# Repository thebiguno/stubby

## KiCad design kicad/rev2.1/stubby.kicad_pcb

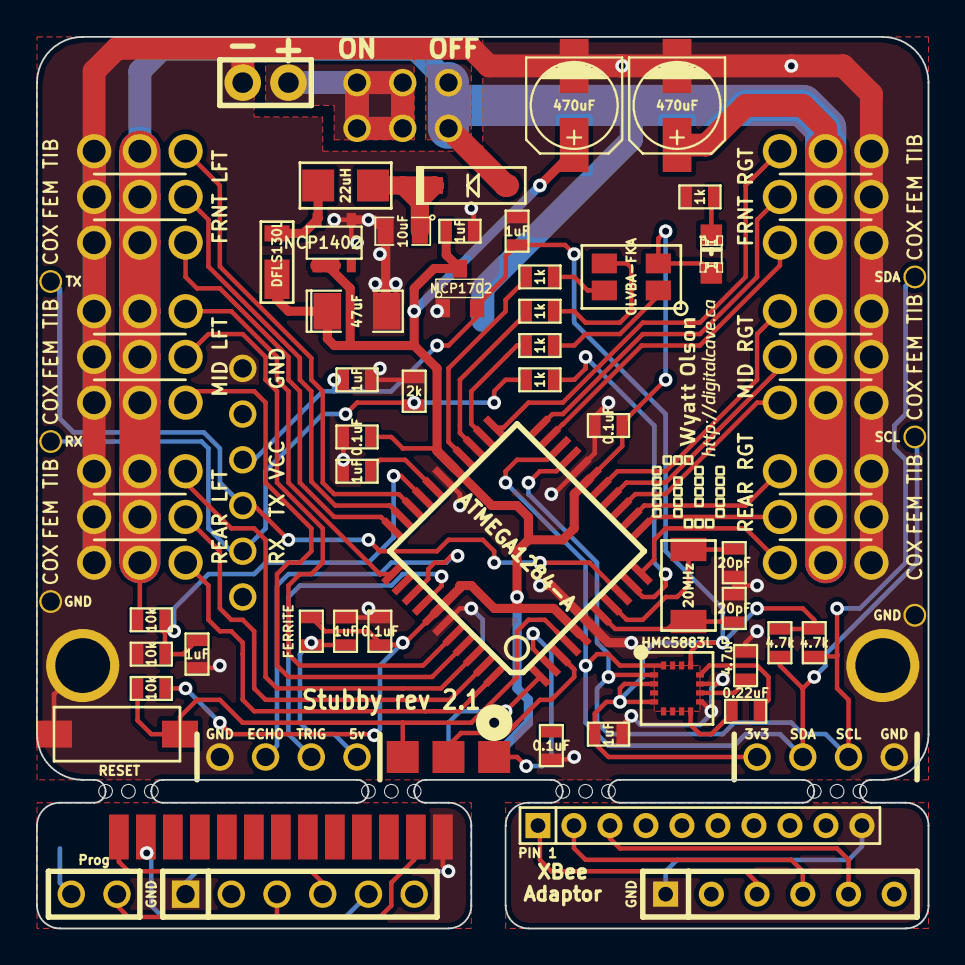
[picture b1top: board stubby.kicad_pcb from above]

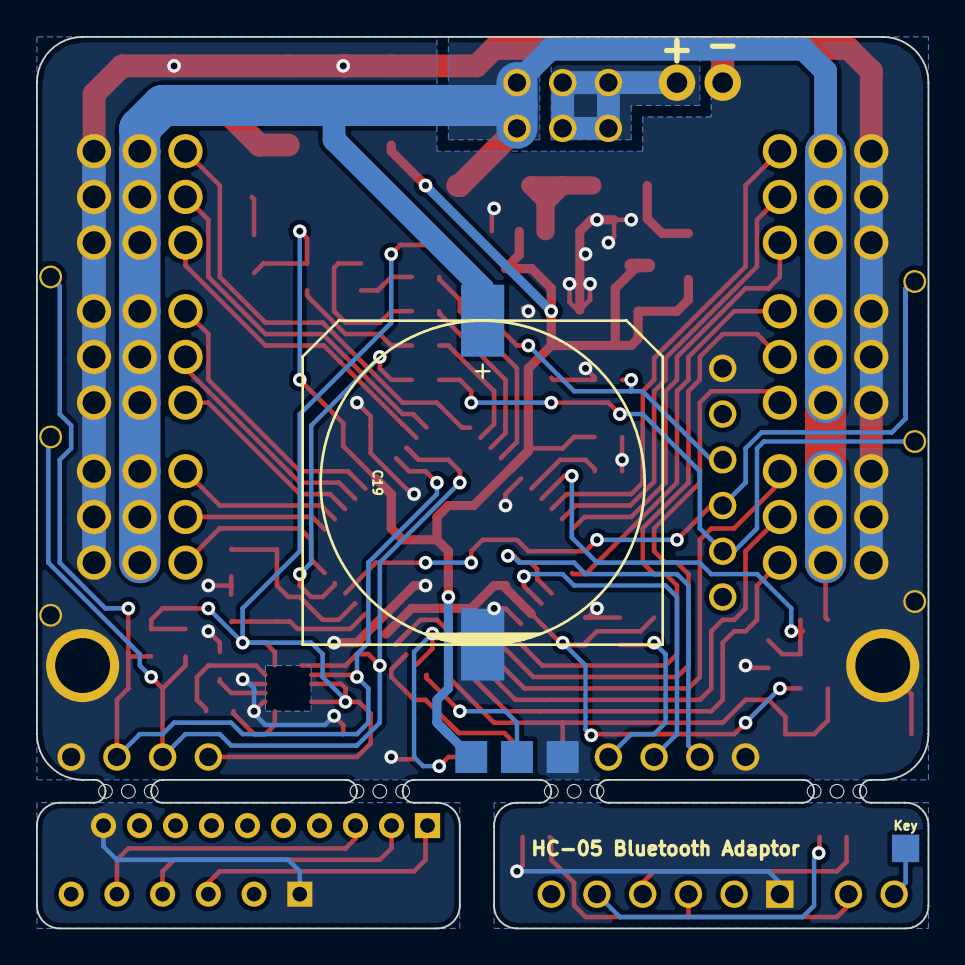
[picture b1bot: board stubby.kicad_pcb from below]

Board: 2 copper layers, 49.5 x 49.5 mm, 74 parts (2 on the bottom side), 60 nets.

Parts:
1PIN, 1PIN#2, 1PIN#3, 1PIN#4, 1PIN#5, 1PIN#6, 1PIN#7, 1PIN#8: P***; 1pin
C1: 10uF; SM0805
C2, C3, C6, C15, C16, C17, C18: 1uF; SM0603_VALUE
C4: 47uF; SM1206POL
C5, C20: 470uF; c_elec_5x5.3
C7: 4.7uF; SM0603_VALUE
C8, C9: 20pF; SM0603_VALUE
C10: 0.22uF; SM0603_VALUE
C11, C12, C13, C14: 0.1uF; SM0603_VALUE
C19: 6800µF; c_elec_18x18
D1: 1N4148W; SOD-123_DIODE
D2: DFLS130L; POWERDI_123
D3: LED; LED-0805-MARKED_ANODE
D4: CLVBA-FKA; 4-PLCC
IC1: ATMEGA1284-A; TQFP44
L1: 22uH; SM1007
L2: FERRITE; SM0603_VALUE
P1, P6, P11: CONN_6; SIL-6
P2, P10: CONN_4; SIL-4
P3: CONN_13; HC05_Edge
P4: CONN_2; SIL-2
P5: CONN_1; SIL-1
P7: CONN_10; SIL-10
P8: BATT (4.8V-6V); SIL-2
P9: PROG; ISP_EDGE
R1, R2: 4.7k; SM0603_VALUE
R3, R5, R6: 10k; SM0603_VALUE
R4, R7, R9, R10, R11: 1k; SM0603_VALUE
R8: 2k; SM0603_VALUE
S1: FRNT LFT; HEX_LEG
S2: FRNT RGT; HEX_LEG_REVERSE
S3: MID LFT; HEX_LEG
S4: MID RGT; HEX_LEG_REVERSE
S5: REAR LFT; HEX_LEG
S6: REAR RGT; HEX_LEG_REVERSE
SW1: SW_PUSH; SW_6x3
SW2: DPDT
U1: HMC5883L; LPCC-16
VAL: DIGITALCAVE_LOGO_WIDE_SMALL
VR1: MCP1702; SOT23
VR2: NCP1402; SOT23-5
X1: 20MHz; CRYSTAL_SMD_5x3.2
mouse_bites: VAL**; mouse_bites
mouse_bites#2, mouse_bites#3, mouse_bites#4: VAL**; mouse_bites

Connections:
+3.3V: C2.1, C15.1, C18.2, P2.1, P11.3, R1.2, R2.2, U1.2, U1.4, U1.13, VR1.3
+5V: C3.1, C4.1, C5.1, C11.1, C12.1, C13.1, D2.2, D3.1, D4.2, IC1.5, IC1.17, IC1.27, IC1.38, L2.2, P9.2, R3.1, VR1.2, VR2.1, VR2.2
+BATT: C19.1, C20.1, D1.1, R5.1, S1.4, S1.5, S1.6, S2.4, S2.5, S2.6, S3.4, S3.5, S3.6, S4.4, S4.5, S4.6, S5.4, S5.5, S5.6, S6.4, S6.5, S6.6, SW2.3, SW2.6
/ADC_BATTERY_METER: C16.2, IC1.30, R5.2, R6.2
/AREF: C6.2, IC1.29
/AVR_RX: 1PIN#6.1, IC1.9, P11.4
/AVR_TX: IC1.10, R7.1
/BATTERY: P8.1, SW2.1, SW2.2, SW2.4, SW2.5
/BLUETOOTH_GND: P1.1, P3.13
/DIST_ECHO: IC1.36, P10.3
/DIST_TRIG: IC1.37, P10.2
/I2C_SCL: 1PIN#3.1, IC1.19, P2.3, R1.1, U1.1
/I2C_SDA: 1PIN#2.1, IC1.20, P2.2, R2.1, U1.16
/LED_BL: IC1.25, R10.1
/LED_BL_R: D4.3, R10.2
/LED_GR: IC1.26, R9.1
/LED_GR_R: D4.4, R9.2
/LED_RD: IC1.24, R11.1
/LED_RD_R: D4.1, R11.2
/MISO: IC1.2, P9.1
/MODULE_RX: 1PIN#5.1, P11.5, R7.2, R8.2
/MOSI: IC1.1, P9.4
/PWM00: IC1.33, S1.1
/PWM01: IC1.32, S1.2
/PWM02: IC1.31, S1.3
/PWM03: IC1.23, S2.1
/PWM04: IC1.22, S2.2
/PWM05: IC1.21, S2.3
/PWM06: IC1.41, S3.1
/PWM07: IC1.40, S3.2
/PWM08: IC1.34, S3.3
/PWM09: IC1.16, S4.1
/PWM10: IC1.15, S4.2
/PWM11: IC1.14, S4.3
/PWM12: IC1.44, S5.1
/PWM13: IC1.43, S5.2
/PWM14: IC1.42, S5.3
/PWM15: IC1.13, S6.1
/PWM16: IC1.12, S6.2
/PWM17: IC1.11, S6.3
/RESET: IC1.4, P9.5, R3.2, SW1.2
/SCK: IC1.3, P9.3
/XBEE_GND: P6.1, P7.10
/XTAL1: C9.2, IC1.8, X1.1
/XTAL2: C8.2, IC1.7, X1.2
GND: 1PIN.1, 1PIN#4.1, 1PIN#7.1, 1PIN#8.1, C1.2, C2.2, C3.2, C4.2, C5.2, C6.1, C7.2, C8.1, C9.1, C11.2, C12.2, C13.2, C14.2, C15.2, C16.1, C17.2, C18.1, C19.2, C20.2, IC1.6, IC1.18, IC1.28, IC1.39, P2.4, P8.2, P9.6, P10.4, P11.1, R4.1, R6.1, R8.1, S1.7, S1.8, S1.9, S2.7, S2.8, S2.9, S3.7, S3.8, S3.9, S4.7, S4.8, S4.9, S5.7, S5.8, S5.9, S6.7, S6.8, S6.9, SW1.1, U1.9, U1.11, VR1.1, VR2.4
unnamed: C7.1, U1.10
unnamed: C10.1, U1.8
unnamed: C10.2, U1.12
unnamed: D2.1, L1.2, VR2.5
unnamed: C1.1, D1.2, L1.1
unnamed: C17.1, L2.1, P10.1
unnamed: D3.2, R4.2
unnamed: P6.3, P7.1
unnamed: P6.4, P7.2
unnamed: P6.5, P7.3
unnamed: P1.5, P3.2
unnamed: P4.1, P5.1
unnamed: P1.4, P3.1
unnamed: P1.3, P3.12, P4.2

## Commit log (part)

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2014-04-16 Renamed stubby and universal controller project folders
2014-04-18 Re-enable the controller; Stubby can now go forward, backwards, turn in place, and (in theory) veer (although the veering is not working great).
2014-04-22 Deleted unused files, and increased stride length
2014-04-23 finished converting to use the new universal controller protocol, which should make for cleaner, more procedural code.
2014-04-24 Change some macro functions to inline functions (more maintainable, just as fast)
2014-04-25 Decrease initial startup delay
2014-04-30 Updated stubby control software to allow a) adjusting delay within the middle of a gait, b) fix bug in the code for veering while moving backwards, c) simplify main loop code
2014-04-30 Re-working Ripple gait to work with current code, as an alternative to tripod. Not quite there yet...
2014-05-21 Rearranging folders
2014-05-24 Changes to code to support new boards
2014-05-26 Adding 3DOF frame + legs, to be cut from 1/4" MDF
2014-05-28 Simple test program to ensure all servos are working properly, with full range of motion
2014-05-29 Adjust comm to not duplicate RX events
2014-05-29 Remove startup delay
2014-05-31 WIP converting Stubby to c++, and moving code around...
2014-06-01 More WIP on IK for Stubby
2014-06-02 Adding three big capacitors to Stubby PCB (1 on 3v3 line to protect against brownouts caused by excessive servo current draw, 2 on the switched battery line)
2014-06-03 Still WIP. All joints seem to be (somewhat) correct, but there is still some error in the output, and setPosition(x,y,z) doesn't seem to give the proper results either.
2014-06-04 Change fuses to use full swing oscillator (higher current draw, but more stable in noisy environments) and to take as long as possible to start up to allow voltage to stabilize.
2014-06-04 Adding degree-based trig lookup functions. Still need to see what sort of speed differences this makes, and whether the decreased accuracy is worth the speedup.
2014-06-15 Updated leg.h with new control rod lengths. IK still not correct; perhaps invalid anles present.
2014-06-16 Exported diagrams into a PDF
2014-06-17 Found a bug in the femur IK calculations which was messing things up. Fixed this bug, updated diagrams + simulation. Now to just try it out on the real robot...
2014-06-18 Updated frame diagram to have PCB facing forward (rather than offset by 30 degrees)
2014-06-19 change servo phase variables to all begin with PHASE_ for readability
2014-06-20 More WIP on trapezoidal drive system
    The tibias and femurs seem to be good now, but the coxas are now all
    wonky. I need to figure out what the neutral angle / E offset / desired
    angle needs to be this system...
2014-06-20 Getting really close... all legs are moving as mirrors of the ones opposite them (which is good), but there is still something wrong with the calculations for the front and back legs; they seem to mo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
2014-06-23 Removed temp angle measurement
2014-06-26 POC on new approach to gait design
    -Using an indexed lookup table for gait steps
    -Main Stubby code needs no knowledge of gait implementation; just pass
    the leg and the step index, and the gait lookup table does the rest
    -Gait code returns an offset point, which is then added to each leg's
    neutral position.
    This commit also includes some main program cleanup, (re) adds support
2014-06-26 Respect offsets again
2014-06-27 Rearranging imports to eliminate circular dependencies
2014-06-28 More work on calibration code; you can now easily calibrate every joint. Also some slight modifications to the gait (raise feet higher)
2014-06-28 Multiple changes to Stubby
    -Rename Leg.get/setOffset() to Leg.get/setCalibration (it makes more
    sense to use the noun 'offset' for the leg offset, not calibration
    offset).
    -Added a distinction between button press (debounced output, only can
    trigger once per button press event) and button hold (will continually
    fire as long as the button is held). Some functions make sense with
2014-06-28 Added a linear translation mode (hold X and use left joystick)
2014-06-28 adjust gait to reduce bouncing
    there is now a 1 step overlap between the part of the cycle where the
    leg is lifted and where the opposite leg is planted.
2014-06-29 Change to calibration
    We now calibrate against the servo neutral angle (rather than the
    desired angle). The raw value which is stored in EEPROM is multiplied
    by 10 and added to the neutral phase when setting the leg positions. To
    find the correct angle to calibrate against, look in Leg.h for the servo
    neutral values.
2014-06-29 Overhaul of status
    Most notably, implementing the battery monitor. We use a running
    average (more correctly, a IIR - Infinite Impuse Response filter). We
    start the ADC once every overflow of timer0 (FCPU/1024) so as not to use
    too many cycles on a very low priority task.
2014-06-29 Delete unused function rotateXY(origin, angle)
    All rotations which I need so far are relative to 0,0,0
2014-07-01 Moving comm.* to lib/universal_controller; this forced Point to also move to lib/.
2014-07-04 Updated the frame diagram to show labels for each part (make assembly a bit easier as the web page can refer to labels)
2014-07-18 Restored rev1 Stubby board (into rev1 sub folder). Adding new rev2 board along side it (rev2 will not replace rev1; it is a different board with different capabilities, but which requires more diffic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
2014-07-22 More work on rev2 PCB; trying to simplify and reduce cost
2014-07-25 Changing to boost converter for 5v output
2014-07-25 Rearranging rev2 still... something seems weird with the component association, may have to revert this commit.
2014-07-29 Moved radio header over... should fit the XBee now (but still need to verify)
2014-07-29 Added some more large value capacitors to 3v3 and 5v lines; changed battery meter to filter out lower frequency shifts (increased resistor + cap values); changed recommended i2c resistor values; mino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
2014-07-29 Enlarged mouse bites to ROUS dimensions
2014-07-31 Shifted SMD pads on bluetooth breakout
2014-08-29 Adding protocol design document
2014-09-01 Moved some more components to the front layer... now there are only four SMD components on the back (2x 100k for battery meter, and 2x 4.7k for I2C bus)
2014-09-01 Cleaned up tracks
2014-09-02 WIP converting Stubby to use new protocol
    This is still very much a WIP, and in fact will not work at all at this
    moment (although it does compile). Currently it is expecting messages
    in the new protocol format from the universal controller; once the UC
    has been updated to send protocol messages, in theory it should work
    identically to how it worked before (i.e. the UC can control Stubby
    directly, but bluetooth control is not implemented). However there are
2014-09-02 Convert universal controller to send new protocol messages, rather than one byte messages from before. Everything compiles, but nothing has been tested yet... testing is for mere mortals.
2014-09-05 1 byte of precision for angles is enough; no need for sending a complete 4 byte float. Adding utils for radians (float) -> byte. Removed Processing powerToggle command.
2014-09-07 Fixed some compile time errors
2014-09-08 WIP Processing API
2014-09-09 Set controller private variables as static volatile
2014-09-10 Trying to calibrate Stubby's inclination to turn...
2014-09-11 WIP on calculations for coxa servos
2014-09-12 -Re-added the simulation -Renamed trig.* to math.* (and added a sqrt_f function, although I am not yet sure if I will use it) -Fixed actual measurements for COXA_X and other Coxa measurements in Leg.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
2014-09-13 Revert recent changes to coxa PWM; back to linear angles rather than trig-generated angles. Very little difference in practice, and the trig is noticeably slower.
2014-09-17 Changed frame diagram to use Adafruit magnetometer rather than Sparkfun one... this is a better board, with faster shipping, for the same total amount.
2014-09-20 Adjusted size of drill holes on diagrams
2014-09-22 Work on rev 2.1... although the more I do it, the more I think it makes sense to just drop it all for now.
2014-09-25 Added a connection from DRDY on the magnetometer to SCK pin
2014-09-26 A bit of cleanup on 2.1
2014-09-27 Code cleanup: move Point to types folder
2014-09-27 WIP on filtering headings. This is actually more difficult than it sounds...
2014-09-27 WIP saving state
2014-09-28 reset legs when using UC after joysticks stopped
2014-09-28 API test program updates
2014-09-30 fix some bugs in previous commit. Still not 100% working yet.
2014-09-30 adjust delays by proper time (measured)
2014-09-30 Fix bug in status init
2014-09-30 Fixed long standing bug in gait rotation code
2014-10-01 Use a PID(ish) approach to ensure turning to the right angle when turning. Still a WIP.
2014-10-01 Added the concept of 'heading verification'
    This happens at the beginning of each heading-dependent operation (move,
    turn, etc). We repeatedly poll the magnetometer until we have a stable
    reading. We then use that reading as the set point for the following
    operation. This appears to work very well; for a short (maybe 0.5
    second) pause before each action, the accuracy of the action goes way
    up.
2014-10-01 Added warning to processing library if magnetometer is not used
2014-10-02 More work on python calibration program.
    Currently, joint calibration, save, and load are working properly. Foot
    calibration will be pretty easy (it will be pretty much a copy / paste
    of joint calibration). Automatic magnetometer calibration will be a bit
    harder.
2014-10-03 More documentation for the python calibration program. It now includes (possibly too much) text describing what is happening and why.
2014-10-04 Updated todo.txt
2014-10-07 Moved all hardware-specific configuration changes to hardware.mk. This keeps things cleaner, and helps to reduce confusion when building custom versions.
2014-10-08 more work on rev 2.1
2014-10-09 convert mcp1702 to sot23 form factor
2014-10-10 Rev 2.1 board changes
    -Removed the resistor and zener from the AVR_RX / MODULE_TX trace. Now
    the module talks directly to the AVR without any interference (there
    were problems with my rev 2.0 board on this item...)
    -Compacted the SMD components a bit more
2014-10-10 slow down timer on faster chips
2014-10-10 cleanup of previous debugging includes
2014-10-10 Moving the 3v3 rail to another regulator, after the 5v one. In rev 2.0, the 5v output is very smooth while the 3v3 output is noisy; this causes the magnetometer to hang when the battery starts to get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
2014-10-10 Added support for HCSR04 Distance Sensor hardware
2014-10-14 Added a 0.1uF cap to magnetometer; redid traces around magnetometer and clock to make for a better layout.
2014-10-15 Updated hardware.mk with proper default values
2014-10-15 Adding heading offset to account for mounting angle of magnetometers
2014-10-16 cosmetic changes to distance sensor area
2014-10-17 Simplified a few traces in the power supply; moved battery indicator capacitor to be further from the rails
2014-10-17 Update text label on rev 1.0 top layer
2014-11-16 fix comment error
2014-12-28 Removed the 5v / 3.3v selector jumper from the rev 2.1 board. It just complicates things. Use a 3.3v FTDI cable if you want a hard-wired connection.
2014-12-30 Moved calibration to python folder; adding WIP controller (Universal Controller)
2014-12-30 Merged Makefile into a single file (with one external config file)
2014-12-31 fix to protocol document
2014-12-31 Added support for 18.432MHz crystal
2015-01-01 working on heat dissipation for ncp1402
2015-01-04 Be a bit more liberal with setting calibration mode
2015-01-07 Adjusted edge cuts based on results from latest board run; fixed ISP Edge solder mask issue
2015-11-02 Changed laser cut design to work with 2.7mm bamboo plywood
2016-01-30 Also allow squrate button to start in UC mode
